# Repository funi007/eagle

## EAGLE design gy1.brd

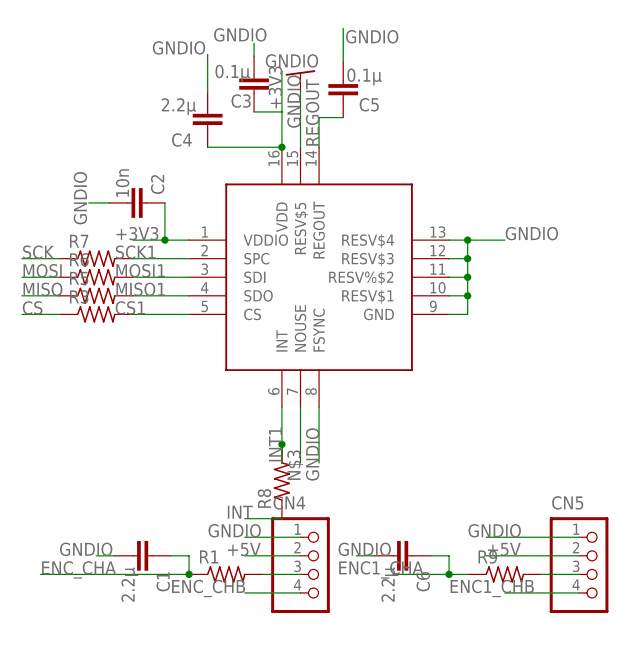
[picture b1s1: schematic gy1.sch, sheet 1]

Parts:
C1, C4, C6: 2.2μ; C0603
C2: 10n; C0603
C3, C5: 0.1μ; C0603
CN4, CN5: S4B-XASK-1
R1, R3, R5, R6, R7, R8, R9: R-US_R0603; R0603
U$1: ICM20602; QFN50P300X300X80-16N

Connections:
+3V3: C2.1, C3.1, C4.1, U$1.1 (VDDIO), U$1.16 (VDD); also elsewhere on the board
+5V: CN4.2, CN5.2; also elsewhere on the board
CS: R3.1; also elsewhere on the board
CS1: R3.2, U$1.5 (CS)
ENC1_CHA: C6.1, R9.1; also elsewhere on the board
ENC1_CHB: CN5.4; also elsewhere on the board
ENC_CHA: C1.1, R1.1; also elsewhere on the board
ENC_CHB: CN4.4; also elsewhere on the board
GNDIO: C1.2, C2.2, C3.2, C4.2, C5.2, C6.2, CN4.1, CN5.1, U$1.8 (FSYNC), U$1.9 (GND), U$1.10 (RESV$1), U$1.11 (RESV%$2), U$1.12 (RESV$3), U$1.13 (RESV$4), U$1.15 (RESV$5); also elsewhere on the board
INT: R8.1
INT1: R8.2, U$1.6 (INT)
MISO: R5.1; also elsewhere on the board
MISO1: R5.2, U$1.4 (SDO)
MOSI: R6.1; also elsewhere on the board
MOSI1: R6.2, U$1.3 (SDI)
unnamed: CN4.3, R1.2
unnamed: CN5.3, R9.2
REGOUT: C5.1, U$1.14 (REGOUT)
SCK: R7.1; also elsewhere on the board
SCK1: R7.2, U$1.2 (SPC)

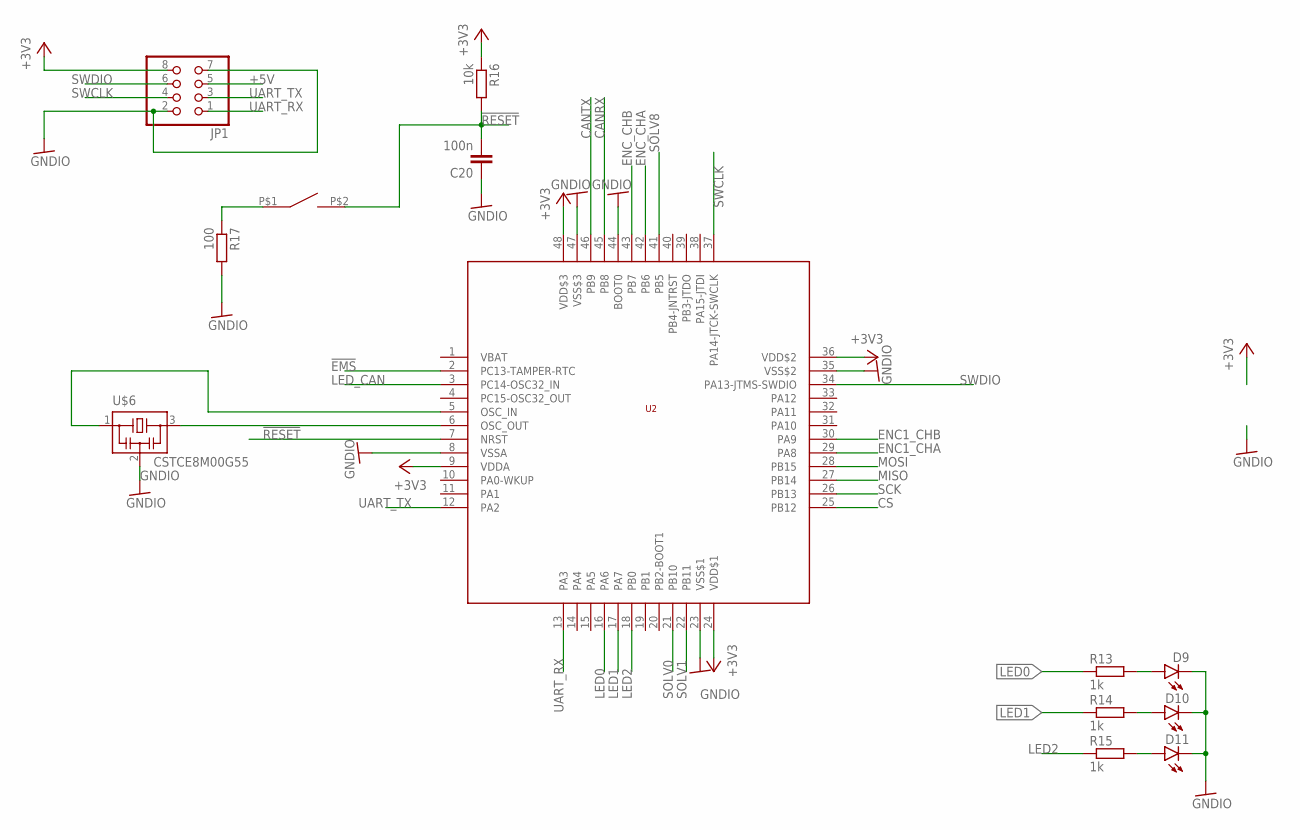
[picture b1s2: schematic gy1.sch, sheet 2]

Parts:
C20: 100n; C0603
D9, D10, D11: LEDCHIPLED_0805; CHIPLED_0805
JP1: PINHD-2X4; 2X04
R13, R14, R15: 1k; R0603
R16: 10k; R0603
R17: 100; R0603
SW1: SWITCH_TACTILETOP; SWITCH_TACTILE_3X6
U2: STM32F103C8; LQFP48
U$6: CSTCE8M00G55

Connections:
!EMS: U2.2 (PC13-TAMPER-RTC)
!RESET: C20.2, R16.2, SW1.P$2 (2), U2.7 (NRST)
+3V3: JP1.8, R16.1, U2.9 (VDDA), U2.24 (VDD$1), U2.36 (VDD$2), U2.48 (VDD$3); also elsewhere on the board
+5V: JP1.5; also elsewhere on the board
CANRX: U2.45 (PB8); also elsewhere on the board
CANTX: U2.46 (PB9); also elsewhere on the board
CS: U2.25 (PB12); also elsewhere on the board
ENC1_CHA: U2.29 (PA8); also elsewhere on the board
ENC1_CHB: U2.30 (PA9); also elsewhere on the board
ENC_CHA: U2.42 (PB6); also elsewhere on the board
ENC_CHB: U2.43 (PB7); also elsewhere on the board
GNDIO: C20.1, D9.C, D10.C, D11.C, JP1.2, JP1.7, R17.2, U2.8 (VSSA), U2.23 (VSS$1), U2.35 (VSS$2), U2.44 (BOOT0), U2.47 (VSS$3), U$6.2; also elsewhere on the board
LED0: R13.1, U2.16 (PA6)
LED1: R14.1, U2.17 (PA7)
LED2: R15.1, U2.18 (PB0)
LED_CAN: U2.3 (PC14-OSC32_IN); also elsewhere on the board
MISO: U2.27 (PB14); also elsewhere on the board
MOSI: U2.28 (PB15); also elsewhere on the board
unnamed: D10.A, R14.2
unnamed: D9.A, R13.2
unnamed: U2.6 (OSC_OUT), U$6.3
unnamed: R17.1, SW1.P$1 (1)
unnamed: U2.5 (OSC_IN), U$6.1
unnamed: D11.A, R15.2
SCK: U2.26 (PB13); also elsewhere on the board
SOLV0: U2.21 (PB10)
SOLV1: U2.22 (PB11)
SOLV8: U2.41 (PB5)
SWCLK: JP1.4, U2.37 (PA14-JTCK-SWCLK)
SWDIO: JP1.6, U2.34 (PA13-JTMS-SWDIO)
UART_RX: JP1.1, U2.13 (PA3)
UART_TX: JP1.3, U2.12 (PA2)

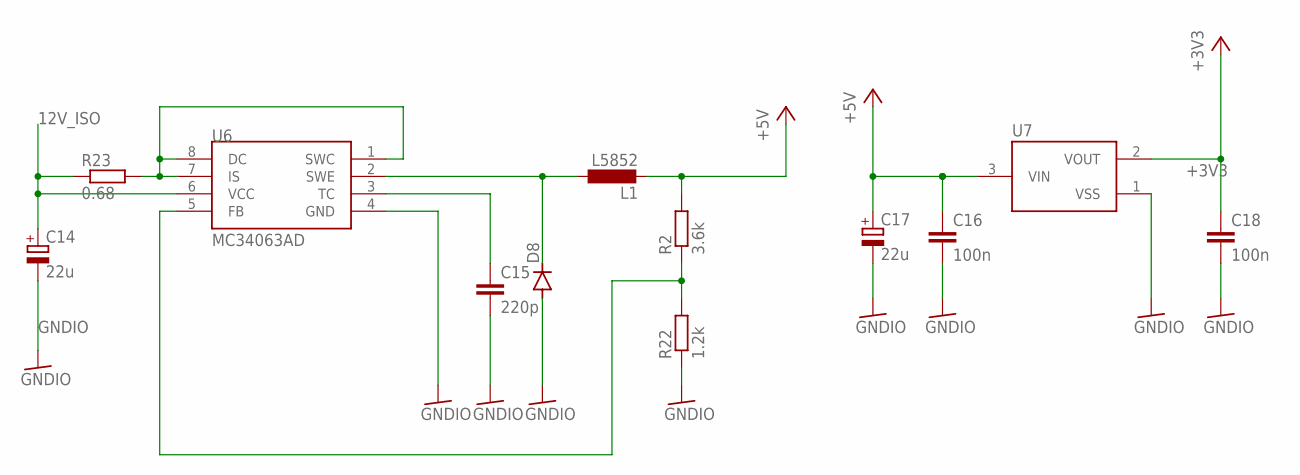
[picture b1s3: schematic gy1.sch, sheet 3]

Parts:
C14, C17: 22u; E2-5
C15: 220p; C0603
C16, C18: 100n; C0603
D8: DIODE-SOD123; SOD123
L1: L5852
R2: 3.6k; R0603
R22: 1.2k; R0603
R23: 0.68; R1206
U6: MC34063AD; SOIC8
U7: XC6206; SOT95P240X110-3

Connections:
12V_ISO: C14.+, R23.1, U6.6 (VCC); also elsewhere on the board
+3V3: C18.1, U7.2 (VOUT); also elsewhere on the board
+5V: C16.1, C17.+, L1.P$2 (2), R2.2, U7.3 (VIN); also elsewhere on the board
GNDIO: C14.-, C15.2, C16.2, C17.-, C18.2, D8.A, R22.1, U6.4 (GND), U7.1 (VSS); also elsewhere on the board
unnamed: R23.2, U6.1 (SWC), U6.7 (IS), U6.8 (DC)
unnamed: D8.C, L1.P$1 (1), U6.2 (SWE)
unnamed: C15.1, U6.3 (TC)
unnamed: R2.1, R22.2, U6.5 (FB)

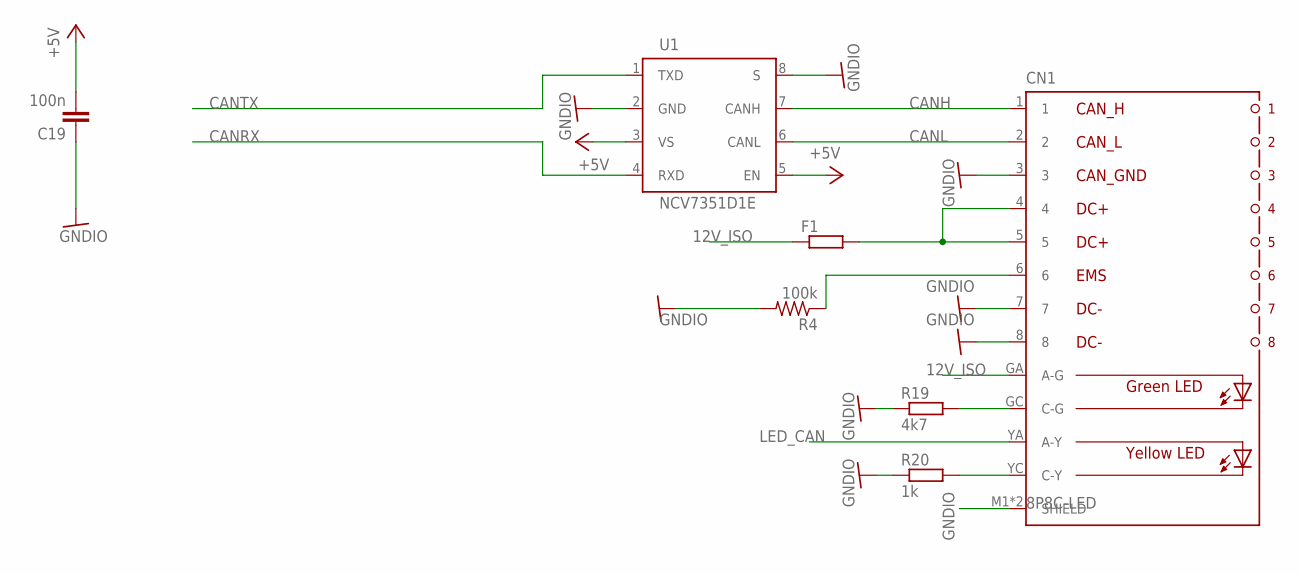
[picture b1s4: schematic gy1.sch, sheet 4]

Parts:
C19: 100n; C0603
CN1: 8P8C-LED
F1: R-EU_R1206; R1206
R4: 100k; R0603
R19: 4k7; R0603
R20: 1k; R0603
U1: NCV7351D1E; SO08

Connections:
12V_ISO: CN1.GA (A-G), F1.1; also elsewhere on the board
+5V: C19.2, U1.3 (VS), U1.5 (EN); also elsewhere on the board
CANH: CN1.1, U1.7 (CANH)
CANL: CN1.2, U1.6 (CANL)
CANRX: U1.4 (RXD); also elsewhere on the board
CANTX: U1.1 (TXD); also elsewhere on the board
GNDIO: C19.1, CN1.3, CN1.7, CN1.8, CN1.M1 (SHIELD), CN1.M2 (SHIELD), R4.2, R19.1, R20.1, U1.2 (GND), U1.8 (S); also elsewhere on the board
LED_CAN: CN1.YA (A-Y); also elsewhere on the board
unnamed: CN1.GC (C-G), R19.2
unnamed: CN1.4, CN1.5, F1.2
unnamed: CN1.YC (C-Y), R20.2
unnamed: CN1.6, R4.1

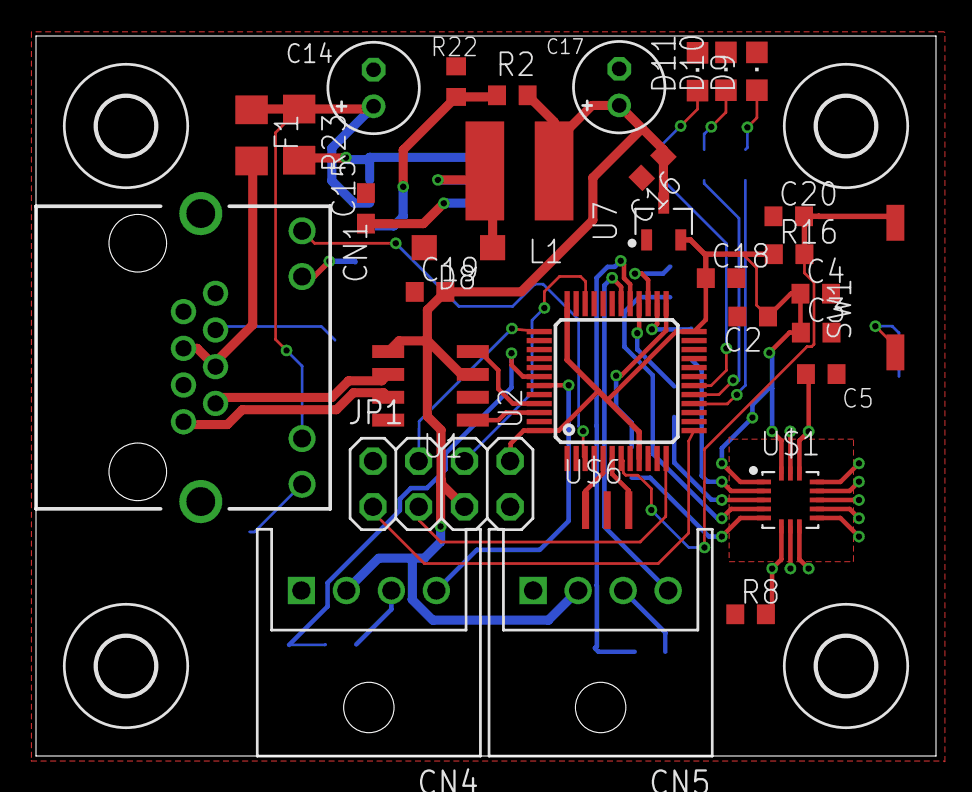
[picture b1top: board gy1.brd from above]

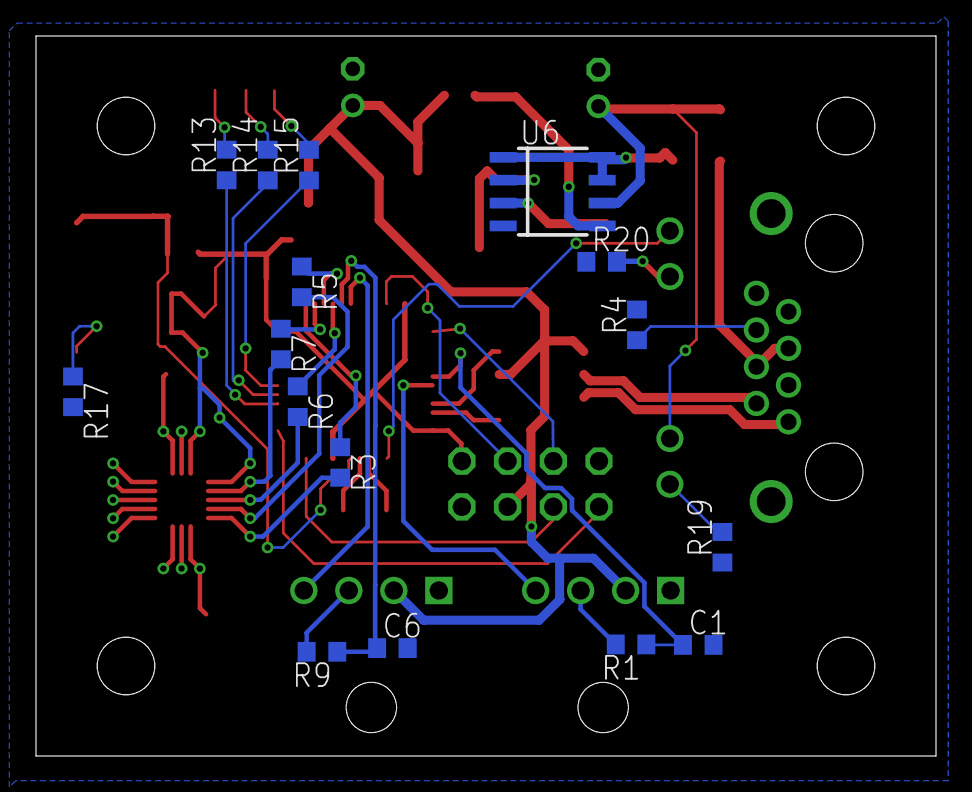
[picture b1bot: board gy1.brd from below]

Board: 2 copper layers, 50.0 x 40.0 mm, 52 parts (16 on the bottom side), 47 nets.

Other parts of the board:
U$2, U$3, U$4, U$5: 3,2

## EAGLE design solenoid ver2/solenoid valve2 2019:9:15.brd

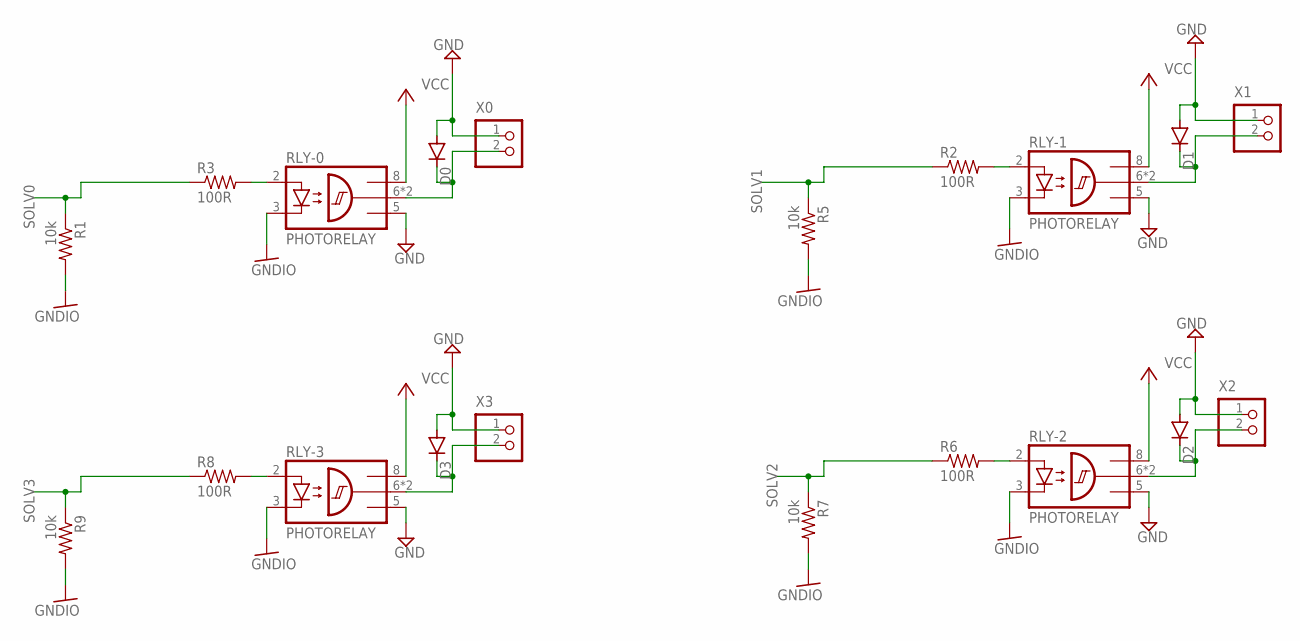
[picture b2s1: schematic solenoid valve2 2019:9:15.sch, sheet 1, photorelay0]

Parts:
D0, D1, D2, D3: DIODE-SOD123; SOD123
R1, R5, R7, R9: 10k; R0603
R2, R3, R6, R8: 100R; R0603
RLY-0, RLY-1, RLY-2, RLY-3: PHOTORELAY; SOP254P1016X385-8
X0, X1, X2, X3: S2B-XASK-1

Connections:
GND: D0.A, D1.A, D2.A, D3.A, RLY-0.5 (GND), RLY-1.5 (GND), RLY-2.5 (GND), RLY-3.5 (GND), X0.1, X1.1, X2.1, X3.1; also elsewhere on the board
GNDIO: R1.2, R5.2, R7.2, R9.2, RLY-0.3 (C), RLY-1.3 (C), RLY-2.3 (C), RLY-3.3 (C); also elsewhere on the board
unnamed: D1.C, RLY-1.6 (OUT), RLY-1.7 (OUT), X1.2
unnamed: R2.2, RLY-1.2 (A)
unnamed: D0.C, RLY-0.6 (OUT), RLY-0.7 (OUT), X0.2
unnamed: D2.C, RLY-2.6 (OUT), RLY-2.7 (OUT), X2.2
unnamed: R3.2, RLY-0.2 (A)
unnamed: R6.2, RLY-2.2 (A)
unnamed: D3.C, RLY-3.6 (OUT), RLY-3.7 (OUT), X3.2
unnamed: R8.2, RLY-3.2 (A)
SOLV0: R1.1, R3.1; also elsewhere on the board
SOLV1: R2.1, R5.1; also elsewhere on the board
SOLV2: R6.1, R7.1; also elsewhere on the board
SOLV3: R8.1, R9.1; also elsewhere on the board
VCC: RLY-0.8 (VCC), RLY-1.8 (VCC), RLY-2.8 (VCC), RLY-3.8 (VCC); also elsewhere on the board

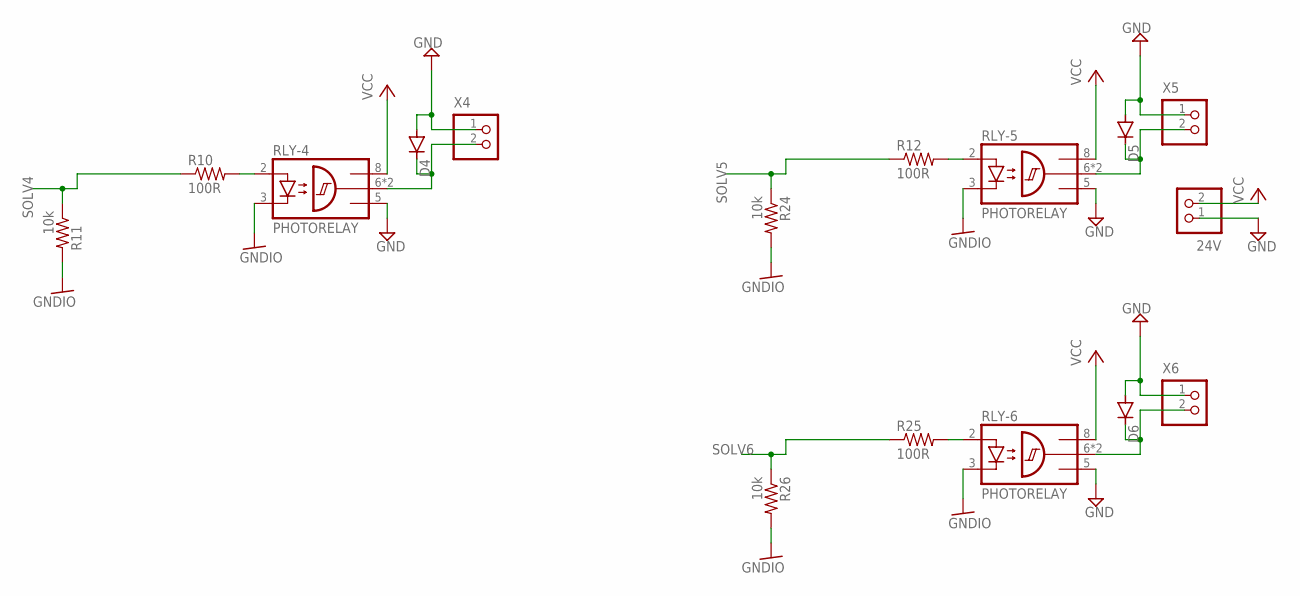
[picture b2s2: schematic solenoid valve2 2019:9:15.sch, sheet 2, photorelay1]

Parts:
24V: S2B-XASK-1
D4, D5, D6: DIODE-SOD123; SOD123
R10, R12, R25: 100R; R0603
R11, R24, R26: 10k; R0603
RLY-4, RLY-5, RLY-6: PHOTORELAY; SOP254P1016X385-8
X4, X5, X6: S2B-XASK-1

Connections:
GND: 24V.1, D4.A, D5.A, D6.A, RLY-4.5 (GND), RLY-5.5 (GND), RLY-6.5 (GND), X4.1, X5.1, X6.1; also elsewhere on the board
GNDIO: R11.2, R24.2, R26.2, RLY-4.3 (C), RLY-5.3 (C), RLY-6.3 (C); also elsewhere on the board
unnamed: D4.C, RLY-4.6 (OUT), RLY-4.7 (OUT), X4.2
unnamed: R10.2, RLY-4.2 (A)
unnamed: D5.C, RLY-5.6 (OUT), RLY-5.7 (OUT), X5.2
unnamed: R12.2, RLY-5.2 (A)
unnamed: D6.C, RLY-6.6 (OUT), RLY-6.7 (OUT), X6.2
unnamed: R25.2, RLY-6.2 (A)
SOLV4: R10.1, R11.1; also elsewhere on the board
SOLV5: R12.1, R24.1; also elsewhere on the board
SOLV6: R25.1, R26.1; also elsewhere on the board
VCC: 24V.2, RLY-4.8 (VCC), RLY-5.8 (VCC), RLY-6.8 (VCC); also elsewhere on the board

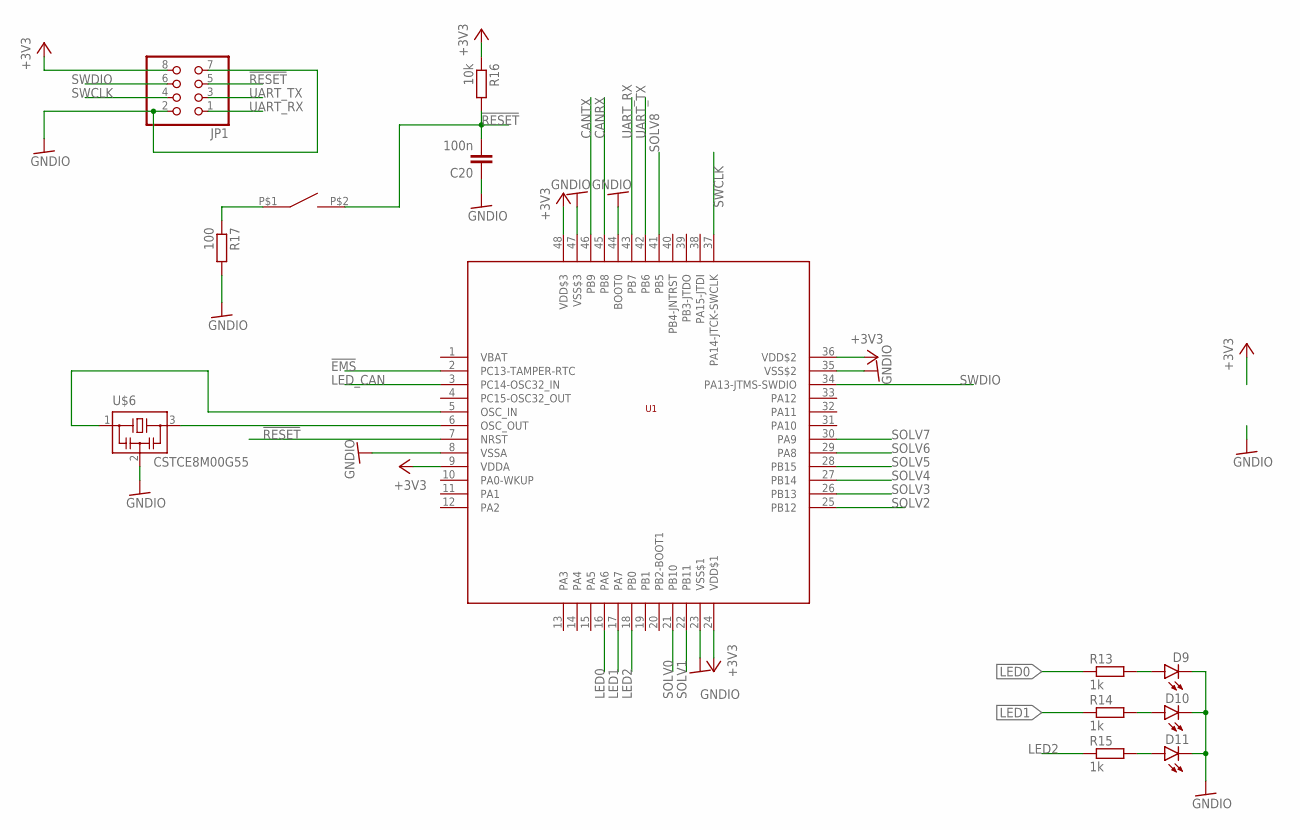
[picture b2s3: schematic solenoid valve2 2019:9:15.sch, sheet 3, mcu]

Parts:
C20: 100n; C0603
D9, D10, D11: LEDCHIPLED_0805; CHIPLED_0805
JP1: PINHD-2X4/90; 2X04/90
R13, R14, R15: 1k; R0603
R16: 10k; R0603
R17: 100; R0603
SW1: SWITCH_TACTILETOP; SWITCH_TACTILE_3X6
U1: STM32F103C8; LQFP48
U$6: CSTCE8M00G55

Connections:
!EMS: U1.2 (PC13-TAMPER-RTC); also elsewhere on the board
!RESET: C20.2, JP1.5, R16.2, SW1.P$2 (2), U1.7 (NRST)
+3V3: JP1.8, R16.1, U1.9 (VDDA), U1.24 (VDD$1), U1.36 (VDD$2), U1.48 (VDD$3); also elsewhere on the board
CANRX: U1.45 (PB8); also elsewhere on the board
CANTX: U1.46 (PB9); also elsewhere on the board
GNDIO: C20.1, D9.C, D10.C, D11.C, JP1.2, JP1.7, R17.2, U1.8 (VSSA), U1.23 (VSS$1), U1.35 (VSS$2), U1.44 (BOOT0), U1.47 (VSS$3), U$6.2; also elsewhere on the board
LED0: R13.1, U1.16 (PA6)
LED1: R14.1, U1.17 (PA7)
LED2: R15.1, U1.18 (PB0)
LED_CAN: U1.3 (PC14-OSC32_IN); also elsewhere on the board
unnamed: D10.A, R14.2
unnamed: D9.A, R13.2
unnamed: U1.6 (OSC_OUT), U$6.3
unnamed: R17.1, SW1.P$1 (1)
unnamed: U1.5 (OSC_IN), U$6.1
unnamed: D11.A, R15.2
SOLV0: U1.21 (PB10); also elsewhere on the board
SOLV1: U1.22 (PB11); also elsewhere on the board
SOLV2: U1.25 (PB12); also elsewhere on the board
SOLV3: U1.26 (PB13); also elsewhere on the board
SOLV4: U1.27 (PB14); also elsewhere on the board
SOLV5: U1.28 (PB15); also elsewhere on the board
SOLV6: U1.29 (PA8); also elsewhere on the board
SOLV7: U1.30 (PA9)
SOLV8: U1.41 (PB5)
SWCLK: JP1.4, U1.37 (PA14-JTCK-SWCLK)
SWDIO: JP1.6, U1.34 (PA13-JTMS-SWDIO)
UART_RX: JP1.1, U1.43 (PB7)
UART_TX: JP1.3, U1.42 (PB6)

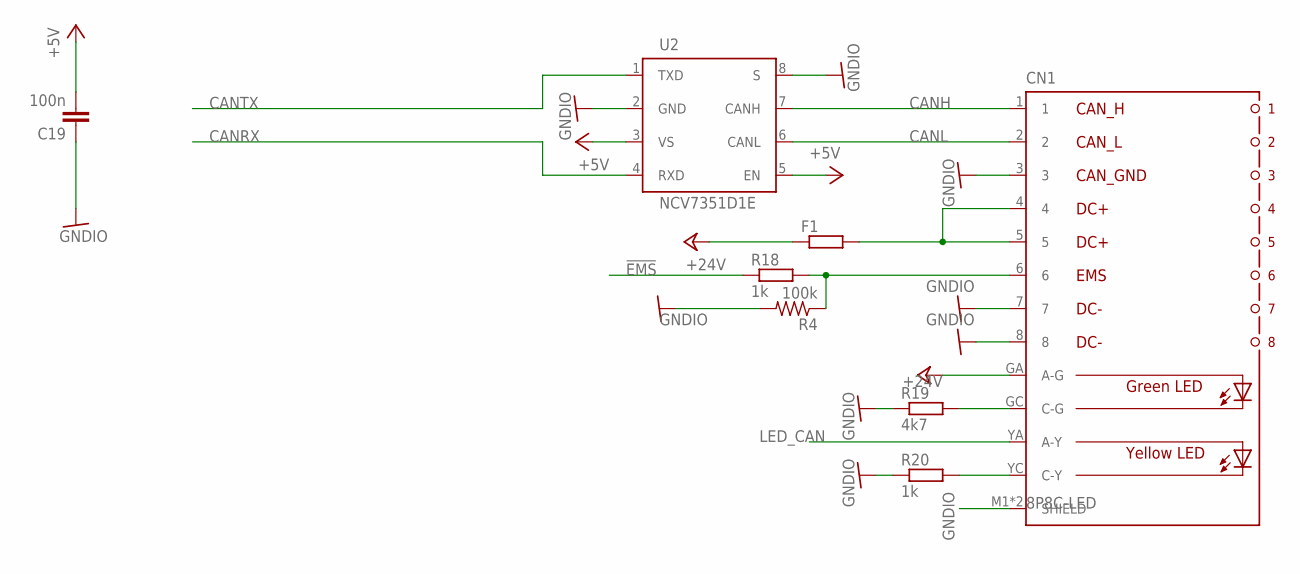
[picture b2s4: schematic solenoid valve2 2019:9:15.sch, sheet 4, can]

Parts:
C19: 100n; C0603
CN1: 8P8C-LED
F1: R-EU_R1206; R1206
R4: 100k; R0603
R18, R20: 1k; R0603
R19: 4k7; R0603
U2: NCV7351D1E; SO08

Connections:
!EMS: R18.1; also elsewhere on the board
+5V: C19.2, U2.3 (VS), U2.5 (EN); also elsewhere on the board
+24V: CN1.GA (A-G), F1.1; also elsewhere on the board
CANH: CN1.1, U2.7 (CANH)
CANL: CN1.2, U2.6 (CANL)
CANRX: U2.4 (RXD); also elsewhere on the board
CANTX: U2.1 (TXD); also elsewhere on the board
GNDIO: C19.1, CN1.3, CN1.7, CN1.8, CN1.M1 (SHIELD), CN1.M2 (SHIELD), R4.2, R19.1, R20.1, U2.2 (GND), U2.8 (S); also elsewhere on the board
LED_CAN: CN1.YA (A-Y); also elsewhere on the board
unnamed: CN1.4, CN1.5, F1.2
unnamed: CN1.YC (C-Y), R20.2
unnamed: CN1.GC (C-G), R19.2
unnamed: CN1.6, R4.1, R18.2

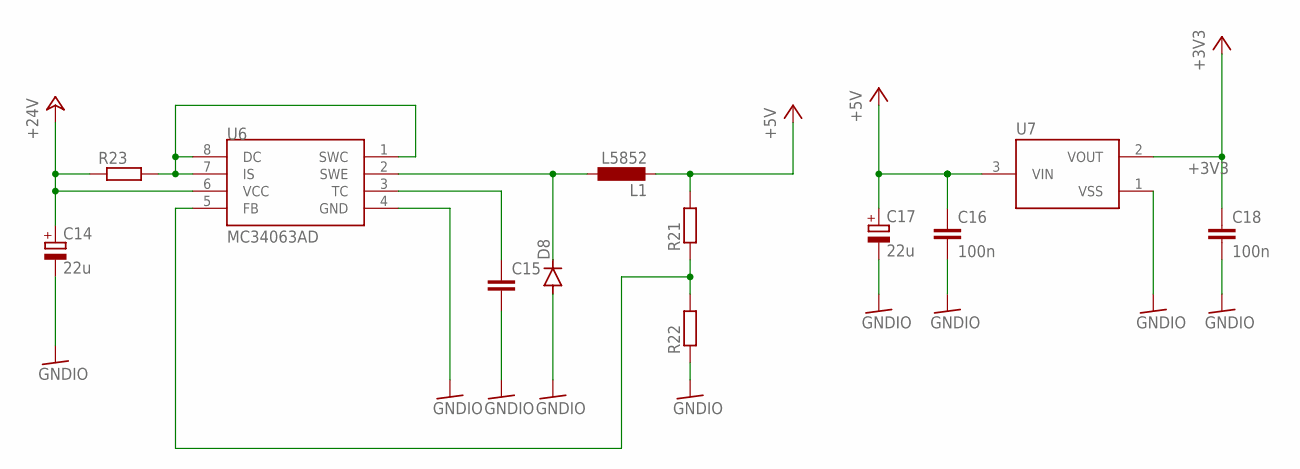
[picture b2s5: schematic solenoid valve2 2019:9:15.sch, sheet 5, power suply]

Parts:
C14, C17: 22u; E2-5
C15: C-EUC0603; C0603
C16, C18: 100n; C0603
D8: DIODE-SOD123; SOD123
L1: L5852
R21, R22: R-EU_R0603; R0603
R23: R-EU_R1206; R1206
U6: MC34063AD; SOIC8
U7: XC6206; SOT95P240X110-3

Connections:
+3V3: C18.1, U7.2 (VOUT); also elsewhere on the board
+5V: C16.1, C17.+, L1.P$2 (2), R21.2, U7.3 (VIN); also elsewhere on the board
+24V: C14.+, R23.1, U6.6 (VCC); also elsewhere on the board
GNDIO: C14.-, C15.2, C16.2, C17.-, C18.2, D8.A, R22.1, U6.4 (GND), U7.1 (VSS); also elsewhere on the board
unnamed: R23.2, U6.1 (SWC), U6.7 (IS), U6.8 (DC)
unnamed: D8.C, L1.P$1 (1), U6.2 (SWE)
unnamed: C15.1, U6.3 (TC)
unnamed: R21.1, R22.2, U6.5 (FB)

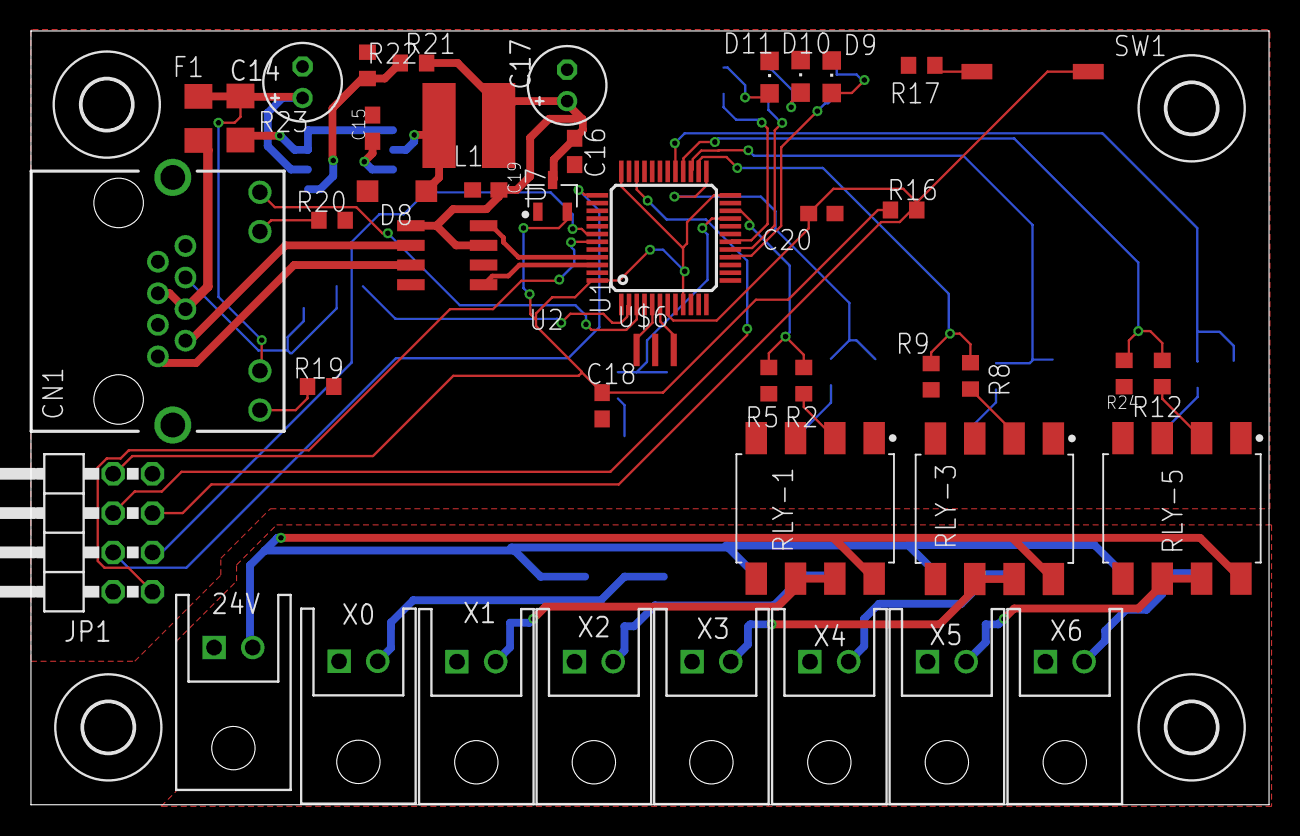
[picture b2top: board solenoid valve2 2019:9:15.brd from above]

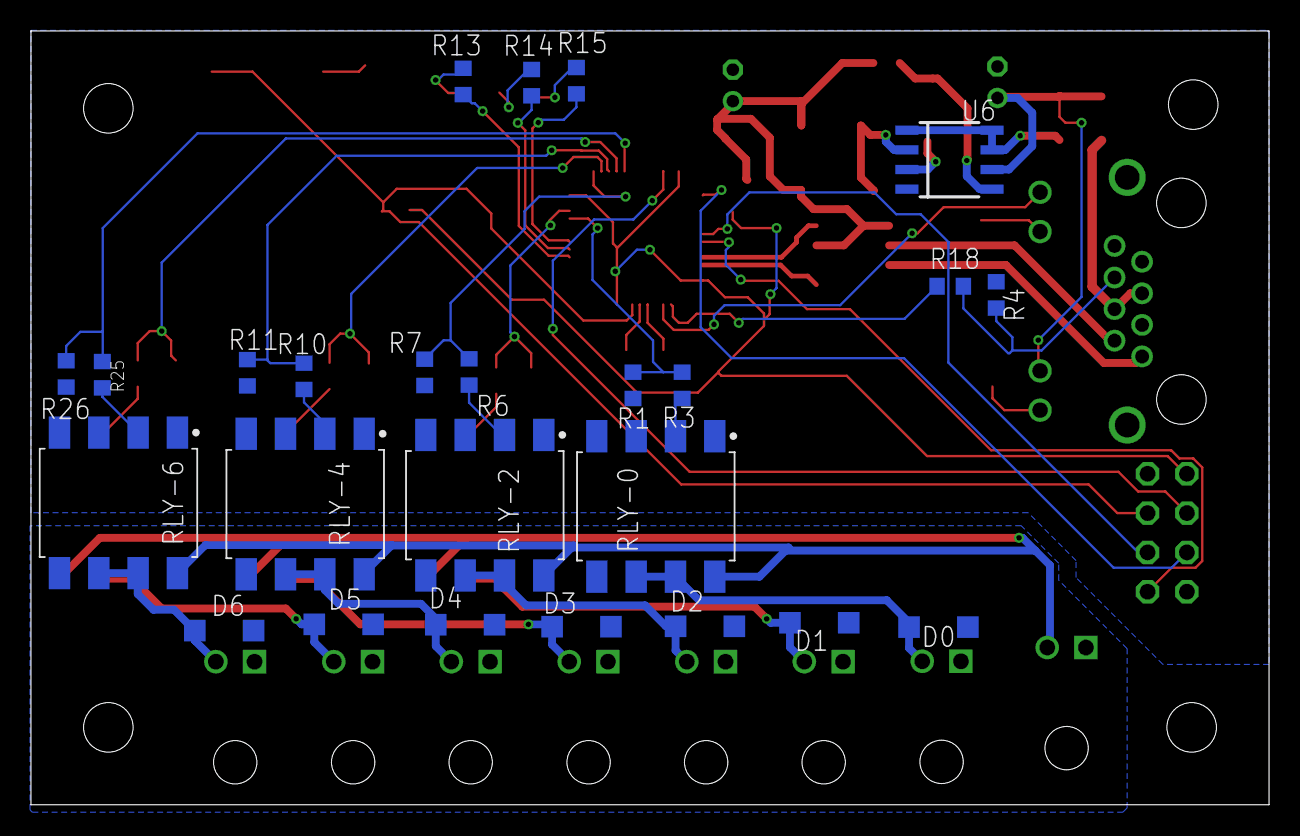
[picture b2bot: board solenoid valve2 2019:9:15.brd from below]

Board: 2 copper layers, 80.0 x 50.0 mm, 73 parts (25 on the bottom side), 55 nets.

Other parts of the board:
U$1, U$2, U$3, U$4: 3,2

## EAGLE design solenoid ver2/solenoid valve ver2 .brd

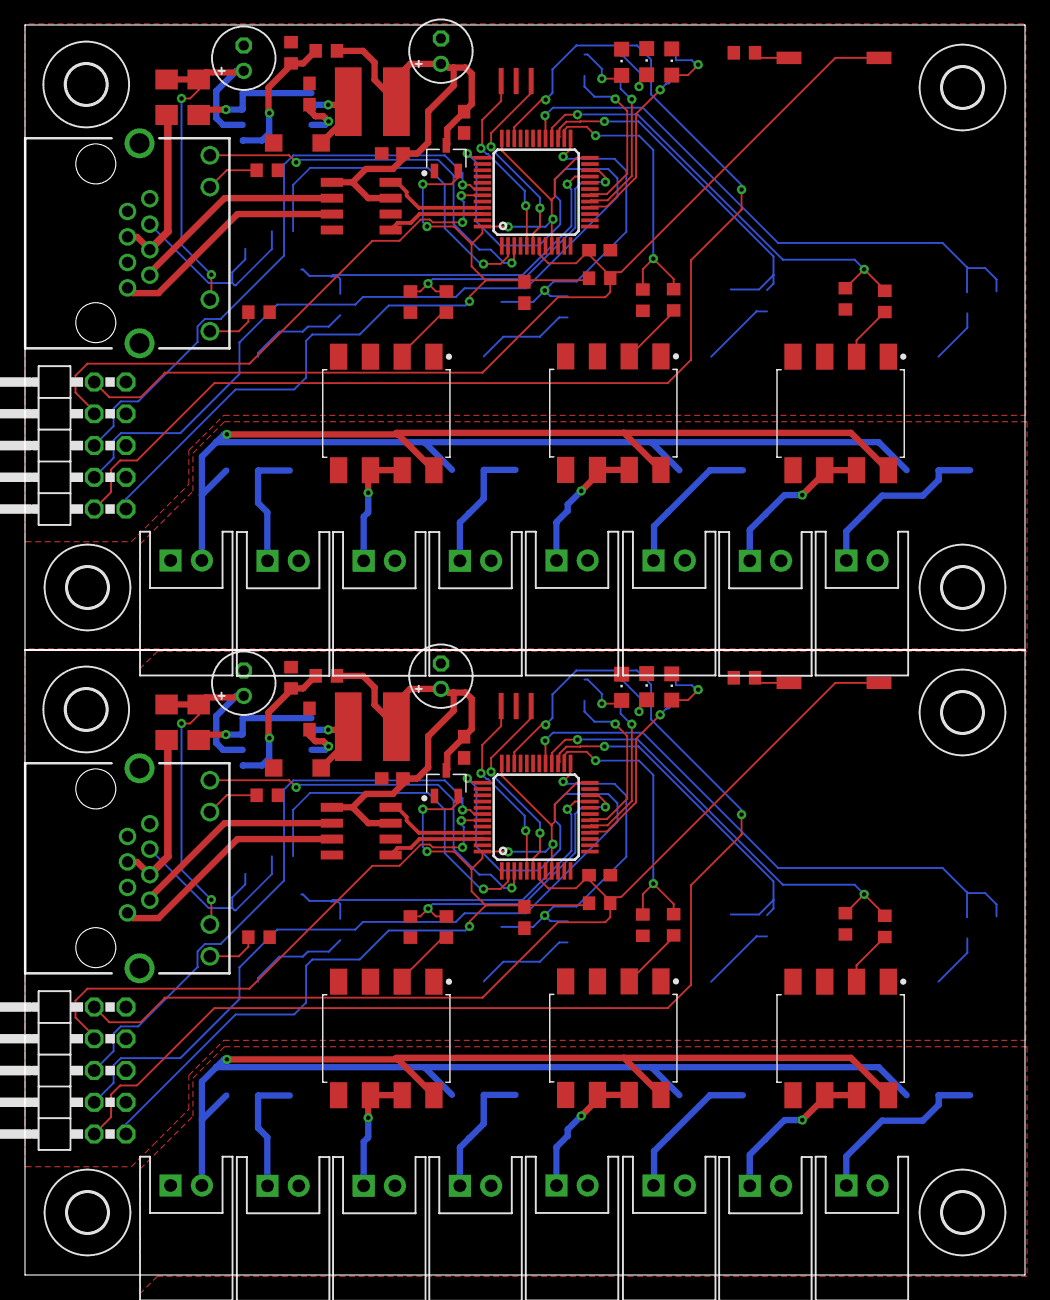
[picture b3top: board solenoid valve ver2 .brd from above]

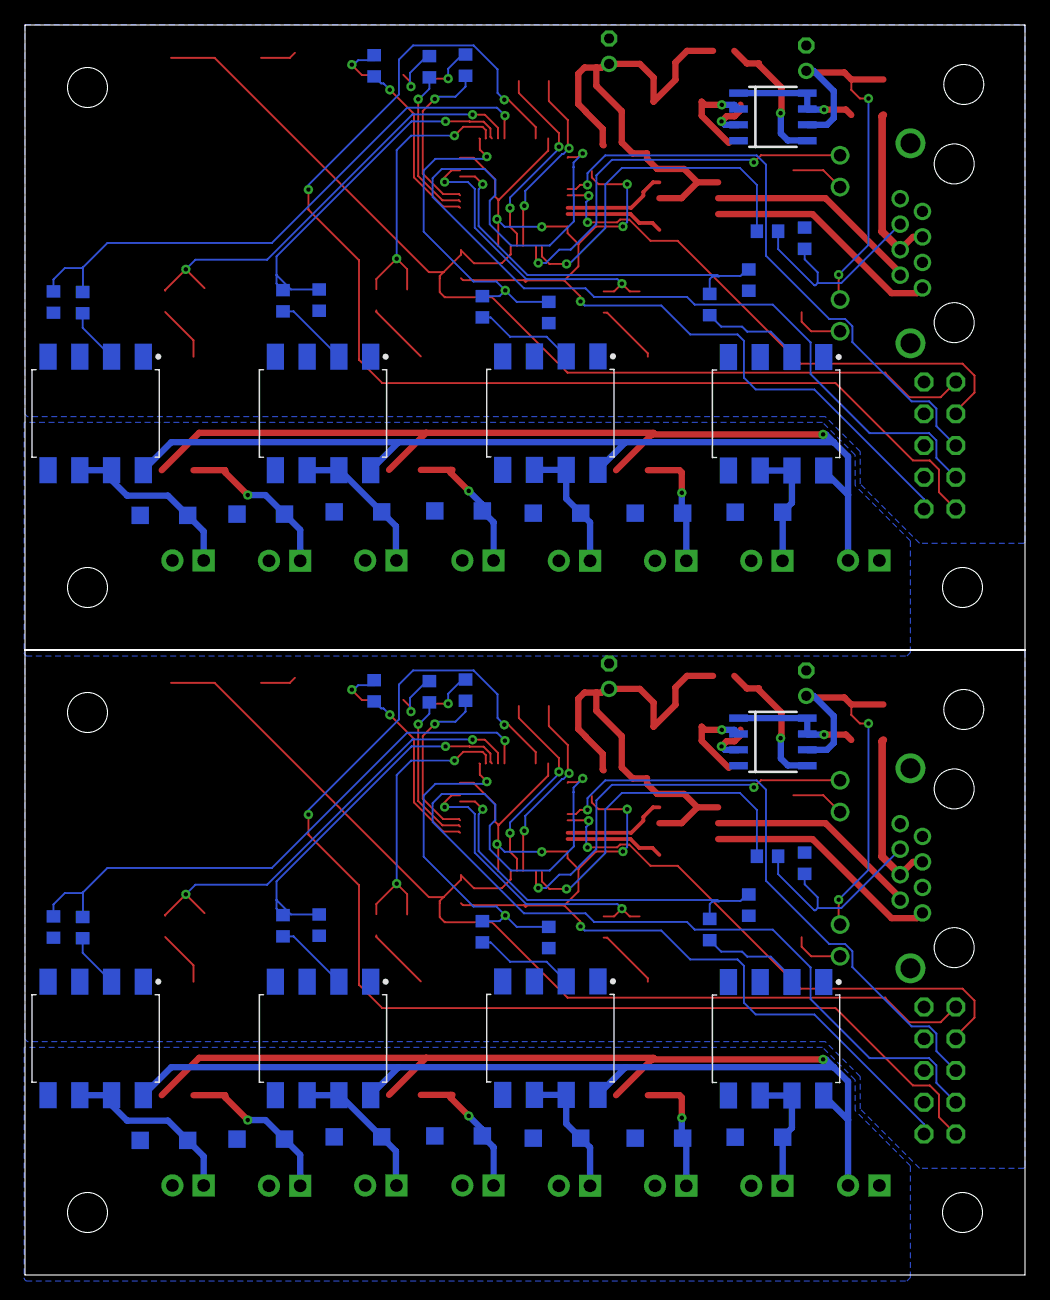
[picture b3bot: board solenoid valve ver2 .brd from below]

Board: 2 copper layers, 80.0 x 100.0 mm, 146 parts (50 on the bottom side), 110 nets.

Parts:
24V, 24V1: S2B-XH-A
C1, C4, C14, C17: 22u; E2-5
C2, C15: C0603
C3, C5, C6, C7, C16, C18, C19, C20: 100n; C0603
CN1, CN2: 8P8C-LED
D1, D2, D3, D4, D5, D6, D7, D8, D12, D15, D16, D17, D18, D19, D20, D21: SOD123
D9, D10, D11, D13, D14, D22: CHIPLED_0805
F1, F2: R1206
JP1, JP2: 2X05/90
L1, L2: L5852
R1, R5, R7, R9, R11, R16, R24, R26, R27, R29, R34, R43, R45, R48, R50, R52: 10k; R0603
R2, R3, R6, R8, R10, R12, R25, R28, R30, R38, R44, R46, R49, R51: 100R; R0603
R4, R47: 100k; R0603
R13, R14, R15, R18, R20, R31, R32, R33, R36, R39: 1k; R0603
R17, R35: 100; R0603
R19, R37: 4k7; R0603
R21, R22, R40, R41: R0603
R23, R42: R1206
RLY-0, RLY-1, RLY-2, RLY-3, RLY-4, RLY-5, RLY-6, RLY-7, RLY-8, RLY-9, RLY-10, RLY-11, RLY-12, RLY-13: PHOTORELAY; SOP254P1016X385-8
SW1, SW2: SWITCH_TACTILETOP; SWITCH_TACTILE_3X6
U1, U3: STM32F103C8; LQFP48
U2, U4: NCV7351D1E; SO08
U5, U6: MC34063AD; SOIC8
U7, U8: XC6206; SOT95P240X110-3
U$1, U$2, U$3, U$4, U$5, U$7, U$8, U$9: 3,2
U$6, U$10: CSTCE8M00G55
X0, X1, X2, X3, X4, X5, X6, X7, X8, X9, X10, X11, X12, X13: S2B-XH-A

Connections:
!EMS: R18.1, U1.2
!EMS1: R36.1, U3.2
!RESET: C20.2, JP2.10, R16.2, SW1.P$2, U1.7
!RESET1: C7.2, JP1.10, R34.2, SW2.P$2, U3.7
+3V1: C5.1, JP1.1, R34.1, U3.9, U3.24, U3.36, U3.48, U8.2
+3V3: C18.1, JP2.1, R16.1, U1.9, U1.24, U1.36, U1.48, U7.2
+5V: C16.1, C17.+, C19.2, L1.P$2, R21.2, U2.3, U2.5, U7.3
+5V1: C3.1, C4.+, C6.2, L2.P$2, R40.2, U4.3, U4.5, U8.3
+24V: C14.+, CN1.GA, F1.1, R23.1, U6.6
+24V1: C1.+, CN2.GA, F2.1, R42.1, U5.6
CANH: CN1.1, U2.7
CANH1: CN2.1, U4.7
CANL: CN1.2, U2.6
CANL1: CN2.2, U4.6
CANRX: U1.45, U2.4
CANRX1: U3.45, U4.4
CANTX: U1.46, U2.1
CANTX1: U3.46, U4.1
GND: 24V.1, D1.A, D2.A, D3.A, D4.A, D5.A, D6.A, D7.A, RLY-0.5, RLY-1.5, RLY-2.5, RLY-3.5, RLY-4.5, RLY-5.5, RLY-6.5, X0.2, X1.2, X2.2, X3.2, X4.2, X5.2, X6.2
GND1: 24V1.1, D12.A, D15.A, D16.A, D17.A, D18.A, D19.A, D20.A, RLY-7.5, RLY-8.5, RLY-9.5, RLY-10.5, RLY-11.5, RLY-12.5, RLY-13.5, X7.2, X8.2, X9.2, X10.2, X11.2, X12.2, X13.2
GNDIO: C14.-, C15.2, C16.2, C17.-, C18.2, C19.1, C20.1, CN1.3, CN1.7, CN1.8, D8.A, D9.C, D10.C, D11.C, JP2.3, R1.2, R4.2, R5.2, R7.2, R9.2, R11.2, R17.2, R19.1, R20.1, R22.1, R24.2, R26.2, RLY-0.3, RLY-1.3, RLY-2.3, RLY-3.3, RLY-4.3, RLY-5.3, RLY-6.3, U1.8, U1.23, U1.35, U1.44, U1.47, U2.2, U2.8, U6.4, U7.1, U$6.2
GNDIO1: C1.-, C2.2, C3.2, C4.-, C5.2, C6.1, C7.1, CN2.3, CN2.7, CN2.8, D13.C, D14.C, D21.A, D22.C, JP1.3, R27.2, R29.2, R35.2, R37.1, R39.1, R41.1, R43.2, R45.2, R47.2, R48.2, R50.2, R52.2, RLY-7.3, RLY-8.3, RLY-9.3, RLY-10.3, RLY-11.3, RLY-12.3, RLY-13.3, U3.8, U3.23, U3.35, U3.44, U3.47, U4.2, U4.8, U5.4, U8.1, U$10.2
LED0: R13.1, U1.16
LED1: R14.1, U1.17
LED2: R15.1, U1.18
LED3: R33.1, U3.18
LED4: R31.1, U3.16
LED5: R32.1, U3.17
LED_CAN: CN1.YA, U1.3
LED_CAN1: CN2.YA, U3.3
unnamed: D2.C, RLY-1.6, RLY-1.7, X1.1
unnamed: R2.2, RLY-1.2
unnamed: D1.C, RLY-0.6, RLY-0.7, X0.1
unnamed: D12.C, RLY-7.6, RLY-7.7, X7.1
unnamed: D3.C, RLY-2.6, RLY-2.7, X2.1
unnamed: R3.2, RLY-0.2
unnamed: R46.2, RLY-7.2
unnamed: R6.2, RLY-2.2
unnamed: D10.A, R14.2
unnamed: D9.A, R13.2
unnamed: U1.6, U$6.3
unnamed: CN1.4, CN1.5, F1.2
unnamed: R23.2, U6.1, U6.7, U6.8
unnamed: D8.C, L1.P$1, U6.2
unnamed: C15.1, U6.3
unnamed: R17.1, SW1.P$1
unnamed: R21.1, R22.2, U6.5
unnamed: CN1.YC, R20.2
unnamed: U1.5, U$6.1
unnamed: D15.C, RLY-8.6, RLY-8.7, X8.1
unnamed: D11.A, R15.2
unnamed: CN1.GC, R19.2
unnamed: D4.C, RLY-3.6, RLY-3.7, X3.1
unnamed: R8.2, RLY-3.2
unnamed: R38.2, RLY-8.2
unnamed: D5.C, RLY-4.6, RLY-4.7, X4.1
unnamed: R10.2, RLY-4.2
unnamed: D16.C, RLY-9.6, RLY-9.7, X10.1
unnamed: D6.C, RLY-5.6, RLY-5.7, X5.1
unnamed: R12.2, RLY-5.2
unnamed: R49.2, RLY-9.2
unnamed: D7.C, RLY-6.6, RLY-6.7, X6.1
unnamed: R25.2, RLY-6.2
unnamed: D17.C, RLY-10.6, RLY-10.7, X9.1
unnamed: R51.2, RLY-10.2
unnamed: D18.C, RLY-11.6, RLY-11.7, X11.1
unnamed: R28.2, RLY-11.2
unnamed: CN1.6, R4.1, R18.2
unnamed: D19.C, RLY-12.6, RLY-12.7, X12.1
unnamed: R30.2, RLY-12.2
unnamed: D20.C, RLY-13.6, RLY-13.7, X13.1
unnamed: R44.2, RLY-13.2
unnamed: D13.A, R32.2
unnamed: D22.A, R31.2
unnamed: U3.5, U$10.1
unnamed: R35.1, SW2.P$1
unnamed: D14.A, R33.2
unnamed: CN2.4, CN2.5, F2.2
unnamed: R42.2, U5.1, U5.7, U5.8
unnamed: D21.C, L2.P$1, U5.2
unnamed: C2.1, U5.3
unnamed: R40.1, R41.2, U5.5
unnamed: CN2.6, R36.2, R47.1
unnamed: U3.6, U$10.3
unnamed: CN2.GC, R37.2
unnamed: CN2.YC, R39.2
SOLV0: R1.1, R3.1, U1.21
SOLV1: R2.1, R5.1, U1.22
SOLV2: R6.1, R7.1, U1.25
SOLV3: R8.1, R9.1, U1.26
SOLV4: R10.1, R11.1, U1.27
SOLV5: R12.1, R24.1, U1.28
SOLV6: R25.1, R26.1, U1.29
SOLV9: R49.1, R50.1, U3.25
SOLV10: R38.1, R48.1, U3.22
SOLV11: R51.1, R52.1, U3.26
SOLV12: R30.1, R43.1, U3.28
SOLV13: R44.1, R45.1, U3.29
SOLV16: R27.1, R46.1, U3.21
SOLV17: R28.1, R29.1, U3.27
SWCLK: JP2.4, U1.37
SWCLK1: JP1.4, U3.37
SWDIO: JP2.2, U1.34
SWDIO1: JP1.2, U3.34
UART_RX: JP2.8, U1.43
UART_RX1: JP1.8, U3.43
UART_TX: JP2.6, U1.42
UART_TX1: JP1.6, U3.42
VCC: 24V.2, RLY-0.8, RLY-1.8, RLY-2.8, RLY-3.8, RLY-4.8, RLY-5.8, RLY-6.8
VCC1: 24V1.2, RLY-7.8, RLY-8.8, RLY-9.8, RLY-10.8, RLY-11.8, RLY-12.8, RLY-13.8

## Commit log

2019-09-13 solenoid
2019-12-31 gyroscope
